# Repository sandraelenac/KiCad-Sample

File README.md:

# Engineering Portfolio

> A collection of electronic hardware design projects developed using both **KiCad** and **Cadence OrCAD Capture/PSpice**.

This repository is organized into two independent design environments:

- **KiCad** — Open-source PCB design projects
- **PSpice** — Cadence OrCAD Capture schematics and SPICE simulations

Each directory contains its own documentation describing the projects, file structure, and how to open the designs.

---

# Repository Structure

```text
KICAD-SAMPLE/
│
├── KICAD/
│   ├── Loow Noise Amplifier (LNA)
│   ├── RX Test ACQ Unit
│
├── PSPICE/
│   ├── README.md
│   ├── A26545-ND/
│   ├── LVDS-PSpiceFiles/
│   ├── REX/
│   ├── TIA_LMH669_1-PSpiceFiles/
│   ├── DESIGN1.DSN
│   ├── DESIGN1.opj
│   ├── DESIGN2.DSN
│   ├── DESIGN2.opj
│   ├── LVDS.DSN
│   ├── LVDS.opj
│   ├── TESTLV.DSN
│   ├── testlv.opj
│   ├── TIA_LMH669_1.DSN
│   └── TIA_LMH669_1.opj
|
├── SQL/
│   ├── README.md
│   ├── Banking Data Base
└── README.md
```

---

# Project Directories

## 📁 KICAD

Contains PCB projects created using **KiCad**.

Included are:

- Electrical schematics
- PCB layouts
- Manufacturing Gerbers
- Drill files
- Pick-and-place files
- Multiple hardware revisions

See:

```text
KICAD/README.md
```

for detailed project information.

---

## 📁 PSPICE

Contains projects created using **Cadence OrCAD Capture** and **PSpice**.

Included are:

- OrCAD schematics
- Simulation projects
- Analog circuit examples
- Differential signaling examples
- Component libraries
- Hardware development projects

See:

```text
PSPICE/README.md
```

for complete documentation.

---

## 📁 SQL

---
# Software Requirements

## KiCad Projects

- KiCad 7+
- KiCad 8/9 compatible

## PSpice Projects

- Cadence OrCAD Capture
- Cadence PSpice

---

# Repository Purpose

This repository serves as a collection of hardware design examples for:

- PCB Design
- Schematic Capture
- Circuit Simulation
- Analog Electronics
- Hardware Revision Control
- Educational Reference
- Future Hardware Development

---

# Repository Organization

| Directory | Description |
|-----------|-------------|
| **KICAD/** | KiCad PCB designs and fabrication files |
| **PSPICE/** | OrCAD Capture schematics and PSpice simulations |

Each directory contains its own **README.md** with project-specific documentation.

---

# Author

**Sandra Castrejon**

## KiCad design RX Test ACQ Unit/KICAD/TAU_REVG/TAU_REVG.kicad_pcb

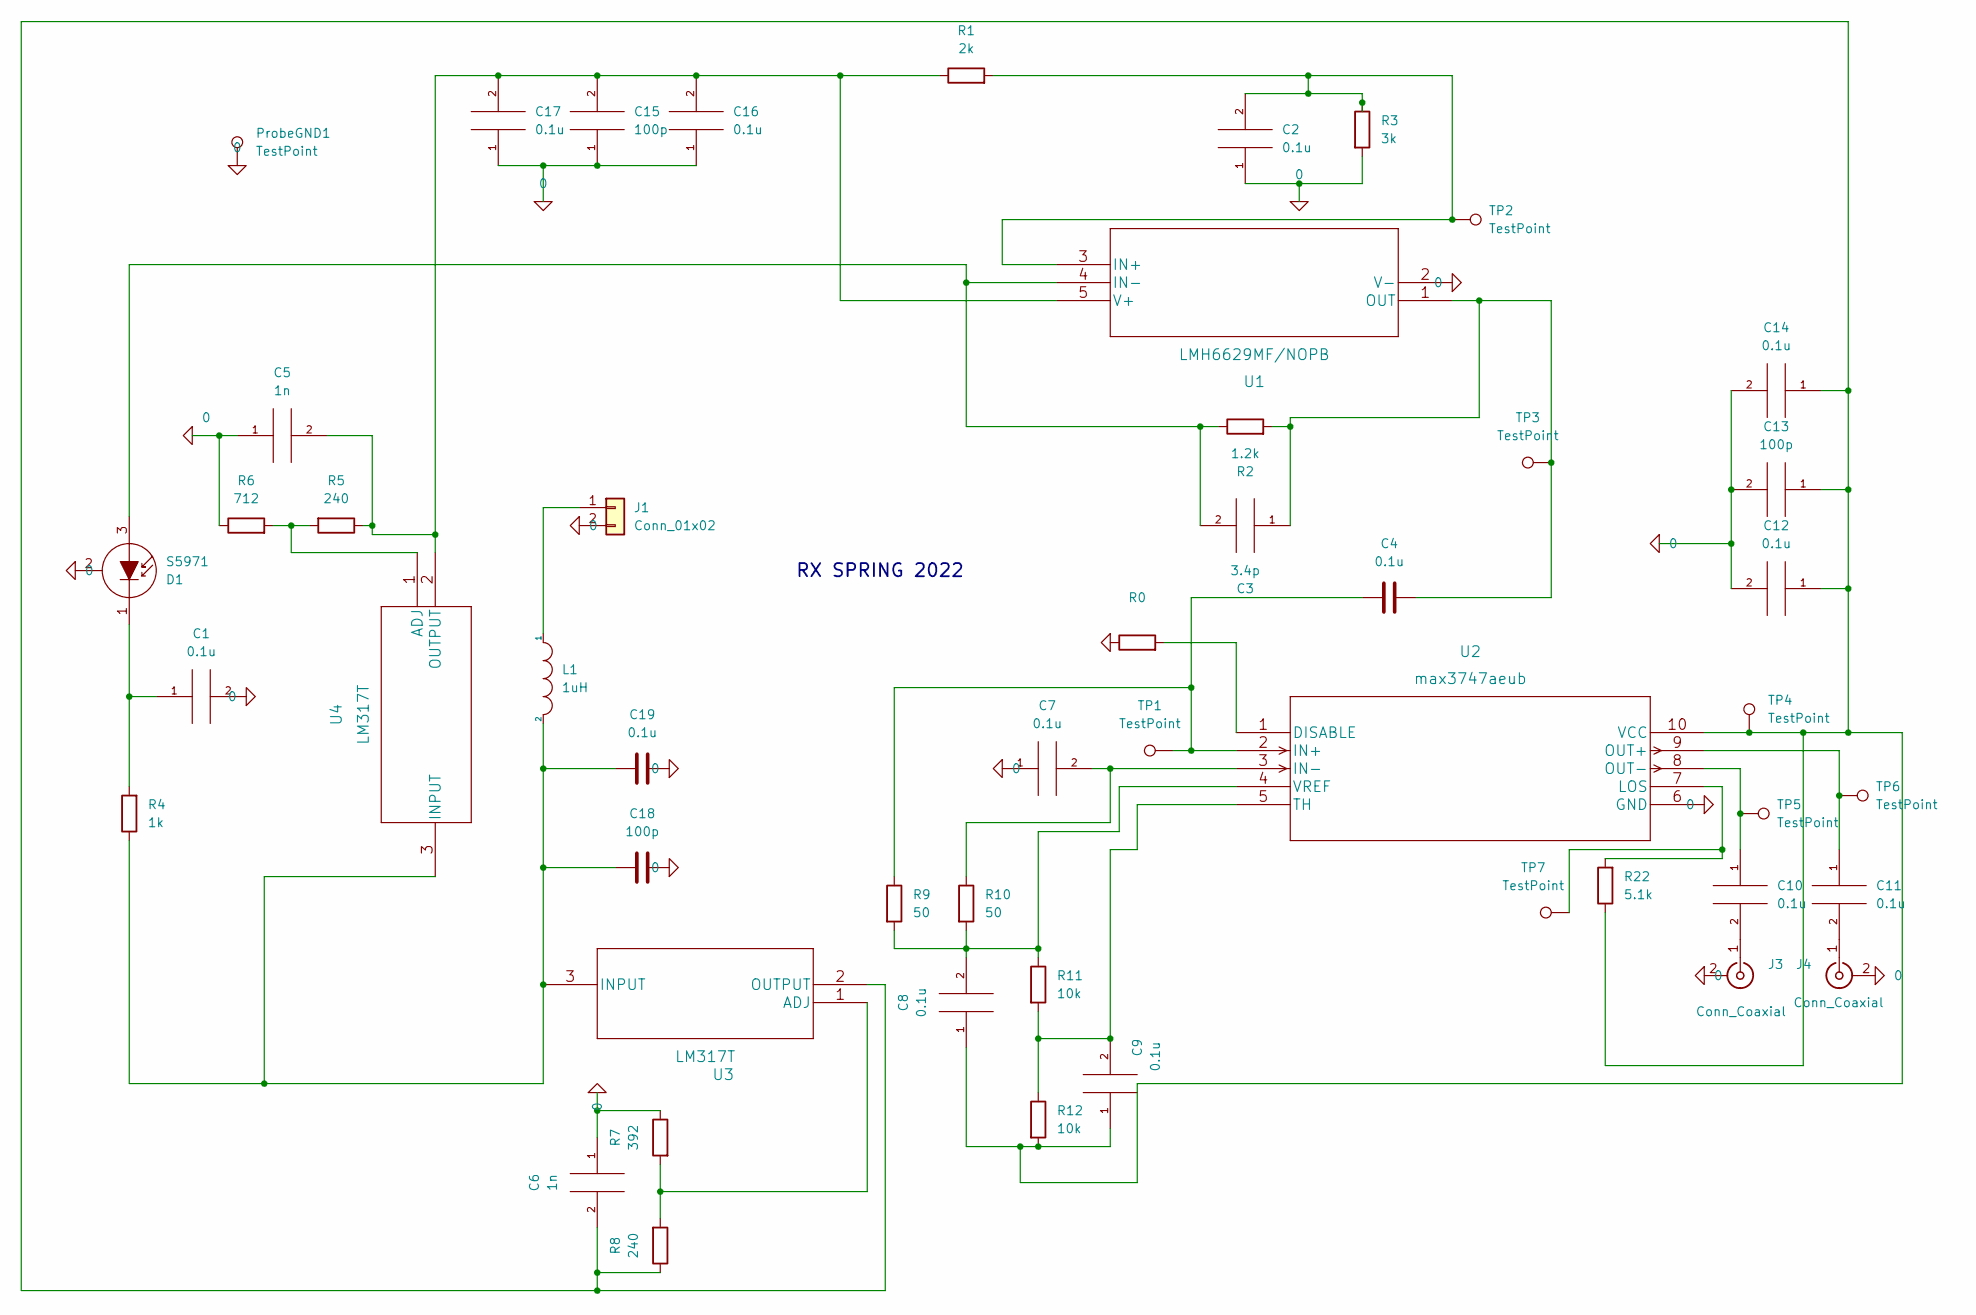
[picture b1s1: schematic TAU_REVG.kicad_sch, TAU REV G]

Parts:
C1, C2, C4, C7, C8, C9, C10, C11, C12, C14, C16, C17, C19: 0.1u; C_0805_2012Metric
C3: 3.4p; C_0805_2012Metric
C5, C6: 1n; C_0805_2012Metric
C13, C15, C18: 100p; C_0805_2012Metric
D1: S5971; TO-18-3
J1: Conn_01x02; Molex_SPOX_5267-02A_1x02_P2.50mm_Vertical
J3, J4: Conn_Coaxial; SMB_Jack_Vertical
L1: 1uH; L_0805_2012Metric
ProbeGND1: TestPoint; TestPoint_Pad_2.0x2.0mm
R0: (no value)
R1: 2k; R_0805_2012Metric
R2: 1.2k; R_0805_2012Metric
R3: 3k; R_0805_2012Metric
R4: 1k; R_0805_2012Metric
R5, R8: 240; R_0805_2012Metric
R6: 712; R_0805_2012Metric
R7: 392; R_0805_2012Metric
R9, R10: 50; R_0805_2012Metric
R11, R12: 10k; R_0805_2012Metric
R22: 5.1k; R_0805_2012Metric
TP1, TP2, TP3, TP4, TP5, TP6, TP7: TestPoint; TestPoint_Pad_2.0x2.0mm
U1: LMH6629MF/NOPB; LMH6629MF&slash_NOPB
U2: max3747aeub
U3, U4: LM317T

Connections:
unnamed: C1.1, D1.1 (K), R4.2
unnamed: C2.2, R1.2, R3.1, TP2.1, U1.3 (IN+)
unnamed: C3.1, C4.2, R2.2, TP3.1, U1.1 (OUT)
unnamed: C3.2, D1.3 (A), R2.1, U1.4 (IN-)
unnamed: C4.1, R9.1, TP1.1, U2.2 (IN+)
unnamed: C7.2, R10.1, U2.3 (IN-)
unnamed: C8.2, R9.2, R10.2, R11.1, U2.4 (VREF)
unnamed: C9.2, R11.2, R12.1, U2.5 (TH)
unnamed: C10.1, TP5.1, U2.8 (OUT-)
unnamed: C10.2, J3.1 (In)
unnamed: C11.1, TP6.1, U2.9 (OUT+)
unnamed: C11.2, J4.1 (In)
unnamed: C6.2, C8.1, C9.1, C12.1, C13.1, C14.1, R8.1, R12.2, R22.1, TP4.1, U2.10 (VCC), U3.2 (OUTPUT)
unnamed: C5.2, C15.2, C16.2, C17.2, R1.1, R5.1, U1.5 (V+), U4.2 (OUTPUT)
unnamed: C18.1, C19.1, L1.2, R4.1, U3.3 (INPUT), U4.3 (INPUT)
unnamed: J1.1, L1.1
unnamed: R5.2, R6.2, U4.1 (ADJ)
unnamed: R7.2, R8.2, U3.1 (ADJ)
unnamed: R22.2, TP7.1, U2.7 (LOS)
unnamed: R0.2, U2.1 (DISABLE)

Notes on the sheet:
RX SPRING 2022

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
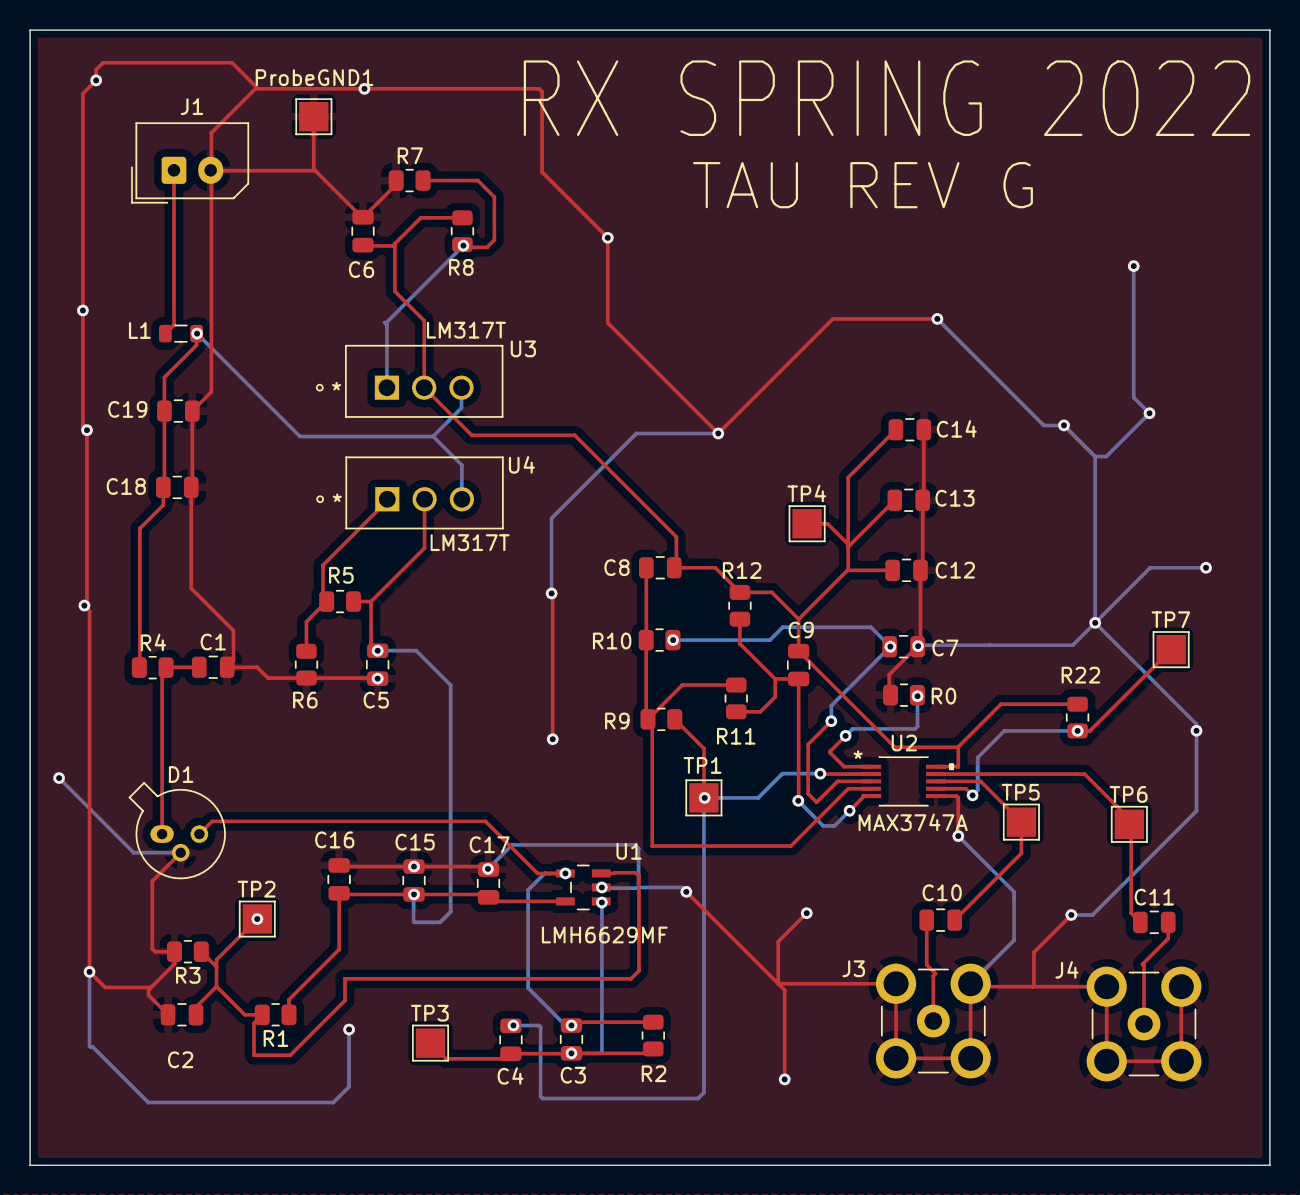
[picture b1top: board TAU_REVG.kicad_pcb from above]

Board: 2 copper layers, 84.5 x 77.3 mm, 50 parts (0 on the bottom side), 21 nets.

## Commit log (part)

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2026-06-28 files added
2026-06-29 READ ME file for KICAD
2026-06-29 READ ME files

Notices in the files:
parts and their libraries:
Copyright 2021 Accelerated Designs. All rights reserved.
